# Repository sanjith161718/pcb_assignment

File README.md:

View this project on [CADLAB.io](https://cadlab.io/project/29316). 

# pcb_assignment

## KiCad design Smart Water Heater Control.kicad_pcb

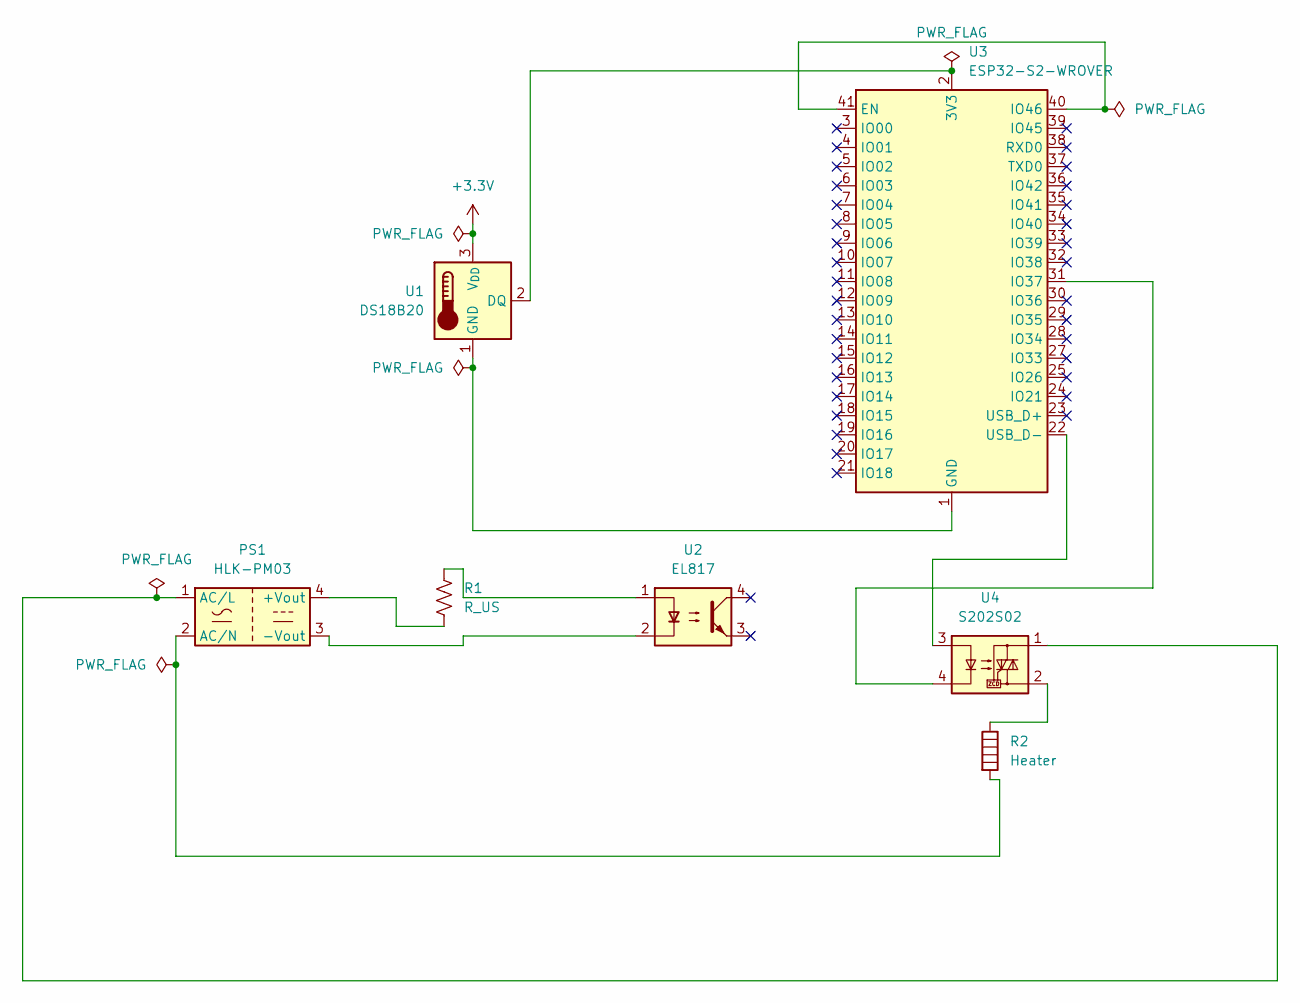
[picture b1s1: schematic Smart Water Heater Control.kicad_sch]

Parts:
PS1: HLK-PM03; Converter_ACDC_Hi-Link_HLK-PMxx
R1: R_US; R_0201_0603Metric
R2: Heater; R_0402_1005Metric
U1: DS18B20; TO-92_Inline
U2: EL817; DIP-4_W7.62mm
U3: ESP32-S2-WROVER
U4: S202S02; SIP4_Sharp-SSR_P7.62mm_Straight

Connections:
+3.3V: U1.3 (V_{DD})
unnamed: PS1.4 (+Vout), R1.2
unnamed: PS1.3 (-Vout), U2.2
unnamed: PS1.1 (AC/L), U4.1
unnamed: PS1.2 (AC/N), R2.2
unnamed: R1.1, U2.1
unnamed: R2.1, U4.2
unnamed: U1.2 (DQ), U3.2 (3V3)
unnamed: U1.1 (GND), U3.1 (GND), U3.26 (GND), U3.42 (GND), U3.43 (GND)
unnamed: U3.40 (IO46), U3.41 (EN)
unnamed: U3.31 (IO37), U4.4
unnamed: U3.22 (USB_D-), U4.3

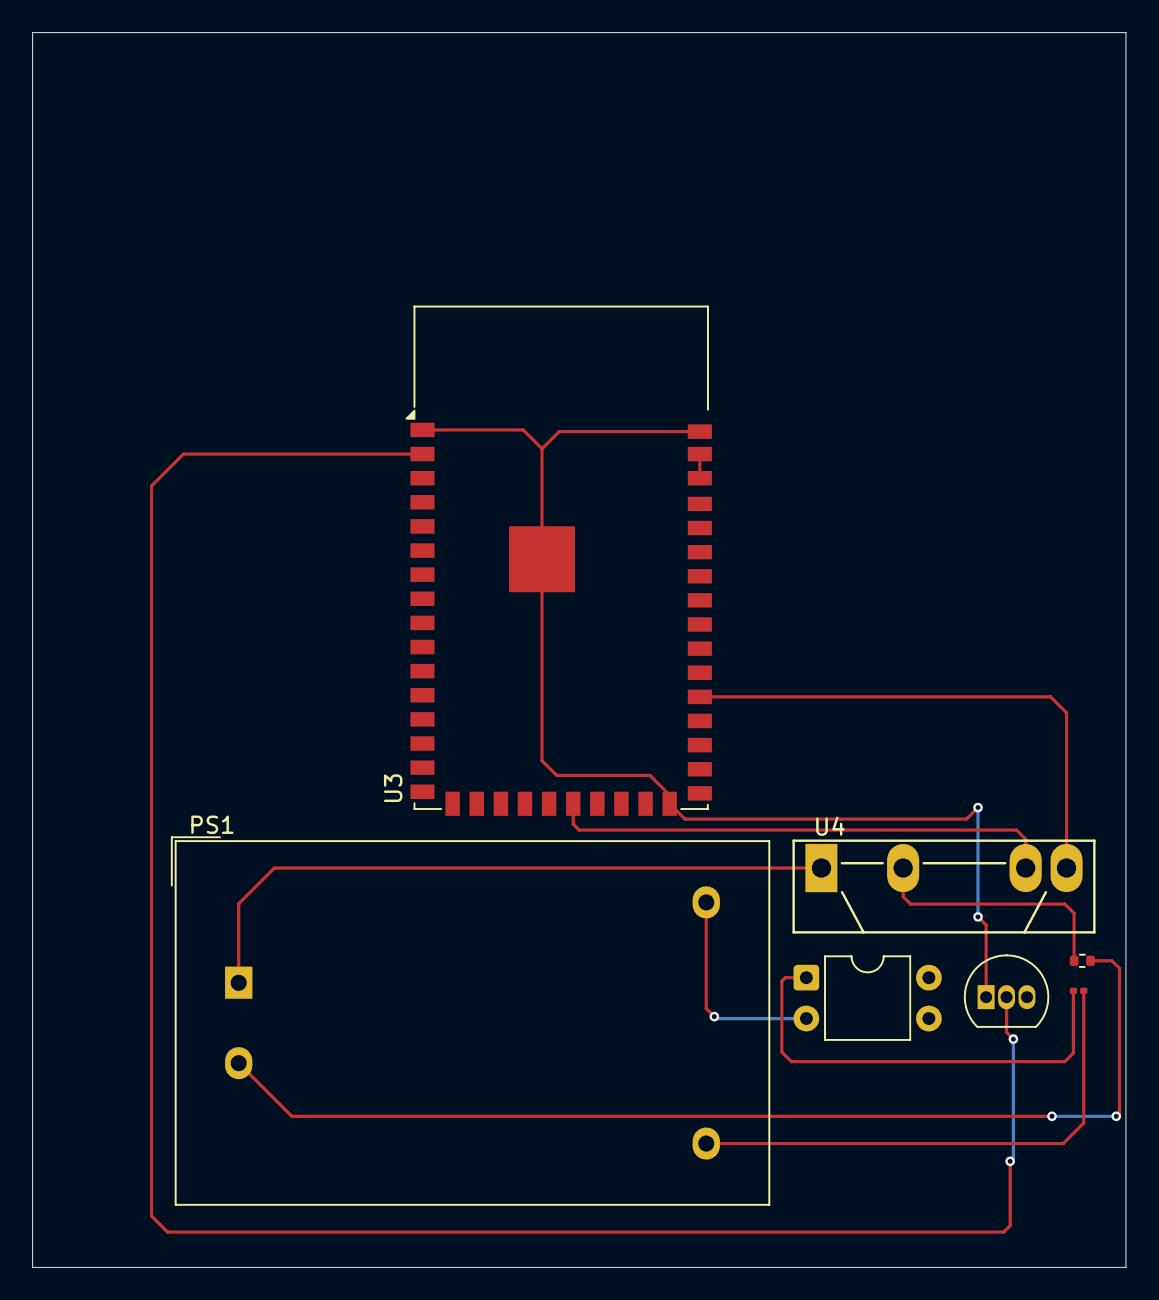
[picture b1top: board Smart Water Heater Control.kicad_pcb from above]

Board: 2 copper layers, 68.0 x 76.8 mm, 7 parts (0 on the bottom side), 11 nets.

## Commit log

2025-04-29 pcb assignment
2025-04-29 Backlink to CADLAB.io has been added.
